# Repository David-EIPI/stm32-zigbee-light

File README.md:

# stm32-zigbee-light
Remotely controlled deck light using a STM32WB55 and Homeassistant integration.

## Overview
This project is yet another automatic outdoor light. Some time back I have purchased a porch light with motion sensor, model 4190 by HeathZenith. My unit apparently was faulty, at least I could not make it to turn on and off at the right time. Instead of returning I have decided to turn it into a practice project to play with Zigbee and Homeassistant.

## Firmware
The firmware is written in C using STM32CubeIDE. I have preserved the link to the IOC file adding a few CPP macro hacks in the source.

The firmware implements 6 endpoints and 12 clusters:
- 6 Analog Output clusters
- 3 Binary Input clusters
- 1 Multistate Value cluster
- 1 Illuminance Measurement cluster
- 1 Temperature Measurement cluster

Zero crossing detection using STM32 timers is described in a [separate file](zerocrossing.md).

## Hardware
The replacement PCB board copies the shape of the original control board and fits in the same enclosure without modifications.

Also the switches, the pot, and the sensors are positioned to fit the holes in the enclosure and the outer case. The firmware reads the switches when not connected to the Zigbee network, otherwise remote settings take precedence.

My setup uses STM32WB55 based board from WeAct, but any other 3.3V controller can be used.

The light is controlled with the triac dimmer triggered by the optocoupler. This configuration is only capable of leading-edge dimming, so a compatible bulb should be used. Phase adjustment (in ms) is needed to compensate for the zero-crossing detection circuit latency (mainly due to the optocoupler).

## ZHA quirck
Homeassistant's Zigbee integration recognizes most clusters from the firmware except the Multistate Value. The quirk file should be copied to the Homeassistant zha_quirk directory for proper work.

(I have edited the auto-generated entity labels visible in the screenshot.)

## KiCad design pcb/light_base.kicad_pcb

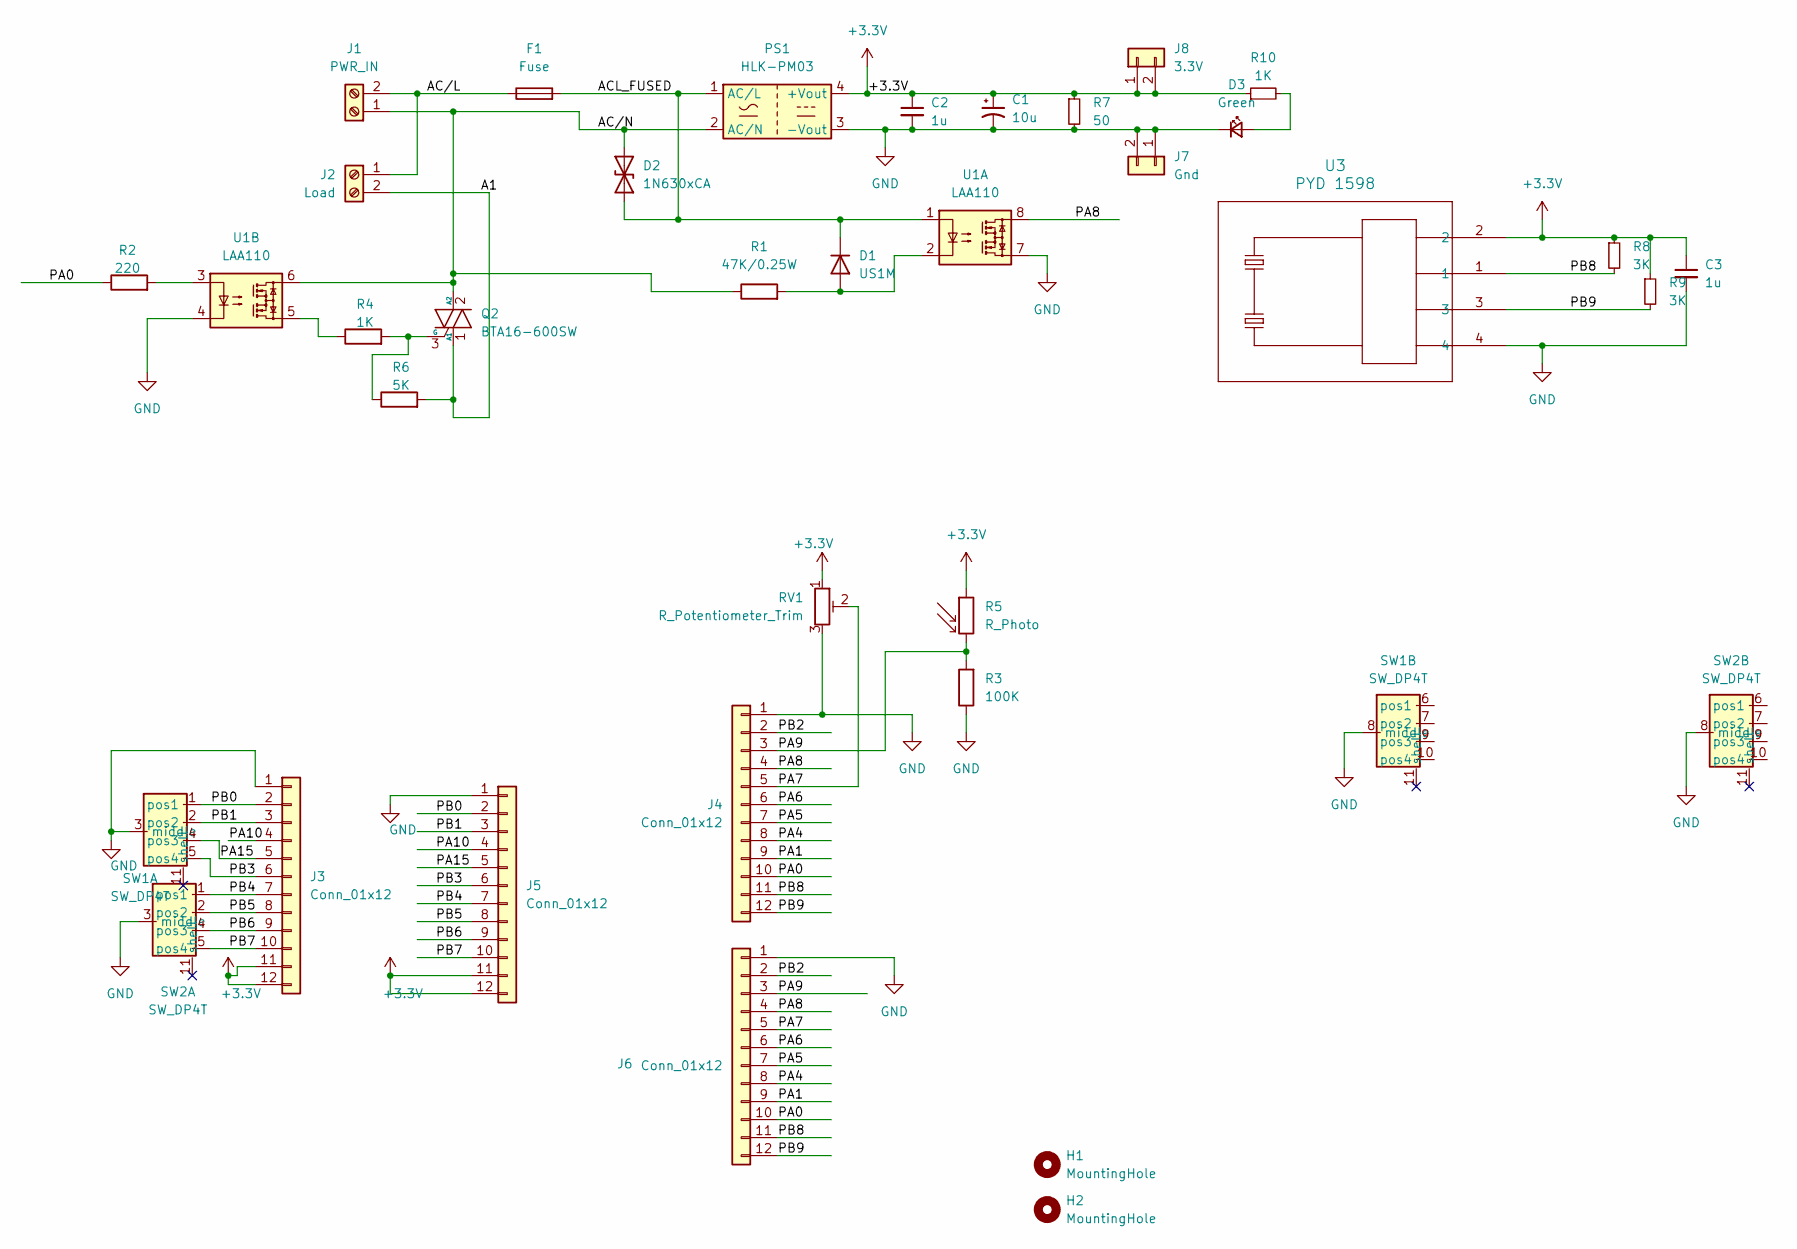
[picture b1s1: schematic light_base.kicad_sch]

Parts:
C1: 10u; CP_Radial_D5.0mm_P2.50mm
C2, C3: 1u; C_0805_2012Metric_Pad1.18x1.45mm_HandSolder
D1: US1M; D_SMA
D2: 1N630xCA; RV_Disc_D9mm_W6.1mm_P5mm
D3: Green; LED_0603_1608Metric_Pad1.05x0.95mm_HandSolder
F1: Fuse; R_Axial_DIN0614_L14.3mm_D5.7mm_P15.24mm_Horizontal
H1, H2: MountingHole; MountingHole_6.4mm_M6
J1: PWR_IN; JST_NV_B02P-NV_1x02_P5.00mm_Vertical
J2: Load; JST_NV_B02P-NV_1x02_P5.00mm_Vertical
J3, J4, J5, J6: Conn_01x12; JST_EH_B12B-EH-A_1x12_P2.50mm_Vertical
J7: Gnd; Molex_KK-254_AE-6410-02A_1x02_P2.54mm_Vertical
J8: 3.3V; Molex_KK-254_AE-6410-02A_1x02_P2.54mm_Vertical
PS1: HLK-PM03; Converter_ACDC_Hi-Link_HLK-PMxx
Q2: BTA16-600SW; TO-220-3_Vertical
R1: 47K/0.25W; R_1206_3216Metric_Pad1.30x1.75mm_HandSolder
R2: 220; R_0603_1608Metric_Pad0.98x0.95mm_HandSolder
R3: 100K; R_0603_1608Metric_Pad0.98x0.95mm_HandSolder
R4: 1K; R_1206_3216Metric_Pad1.30x1.75mm_HandSolder
R5: R_Photo; R_LDR_7x6mm_P5.1mm_Vertical
R6: 5K; R_1206_3216Metric_Pad1.30x1.75mm_HandSolder
R7: 50; R_0805_2012Metric_Pad1.20x1.40mm_HandSolder
R8, R9: 3K; R_0603_1608Metric_Pad0.98x0.95mm_HandSolder
R10: 1K; R_0603_1608Metric_Pad0.98x0.95mm_HandSolder
RV1: R_Potentiometer_Trim; Potentiometer_Piher_PT-10-V10_Vertical_Hole
SW1, SW2: SW_DP4T
U1: LAA110; DIP-8_W7.62mm
U3: PYD 1598; SENSE4_PYD 1598_EXT

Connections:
+3.3V: C1.1, C2.1, C3.1, J3.11, J3.12, J5.11, J5.12, J8.1, J8.2, PS1.4 (+Vout), R5.1, R7.1, R8.1, R9.1, R10.1, RV1.1, U3.2
/A1: J2.2, Q2.1 (A1), R6.2
/ACL_FUSED: D1.1 (K), D2.1 (A1), F1.2, PS1.1 (AC/L), U1.1
/AC/L: F1.1, J1.2, J2.1
/AC/N: D2.2 (A2), J1.1, PS1.2 (AC/N), Q2.2 (A2), R1.1, U1.6
/PA0: J4.10, J6.10, R2.1
/PA1: J4.9, J6.9
/PA4: J4.8, J6.8
/PA5: J4.7, J6.7
/PA6: J4.6, J6.6
/PA7: J4.5, J6.5, RV1.2
/PA8: J4.4, J6.4, U1.8
/PA9: J4.3, J6.3, R3.2, R5.2
/PA10: J3.4, J5.4
/PA15: J3.5, J5.5, SW1.4 (pos3)
/PB0: J3.2, J5.2, SW1.1 (pos1)
/PB1: J3.3, J5.3, SW1.2 (pos2)
/PB2: J4.2, J6.2
/PB3: J3.6, J5.6, SW1.5 (pos4)
/PB4: J3.7, J5.7, SW2.1 (pos1)
/PB5: J3.8, J5.8, SW2.2 (pos2)
/PB6: J3.9, J5.9, SW2.4 (pos3)
/PB7: J3.10, J5.10, SW2.5 (pos4)
/PB8: J4.11, J6.11, R8.2, U3.1
/PB9: J4.12, J6.12, R9.2, U3.3
GND: C1.2, C2.2, C3.2, D3.1 (K), J3.1, J4.1, J5.1, J6.1, J7.1, J7.2, PS1.3 (-Vout), R3.1, R7.2, RV1.3, SW1.3 (middle), SW1.8 (middle), SW2.3 (middle), SW2.8 (middle), U1.4, U1.7, U3.4
unnamed: D1.2 (A), R1.2, U1.2
unnamed: D3.2 (A), R10.2
unnamed: Q2.3 (G), R4.2, R6.1
unnamed: R2.2, U1.3
unnamed: R4.1, U1.5

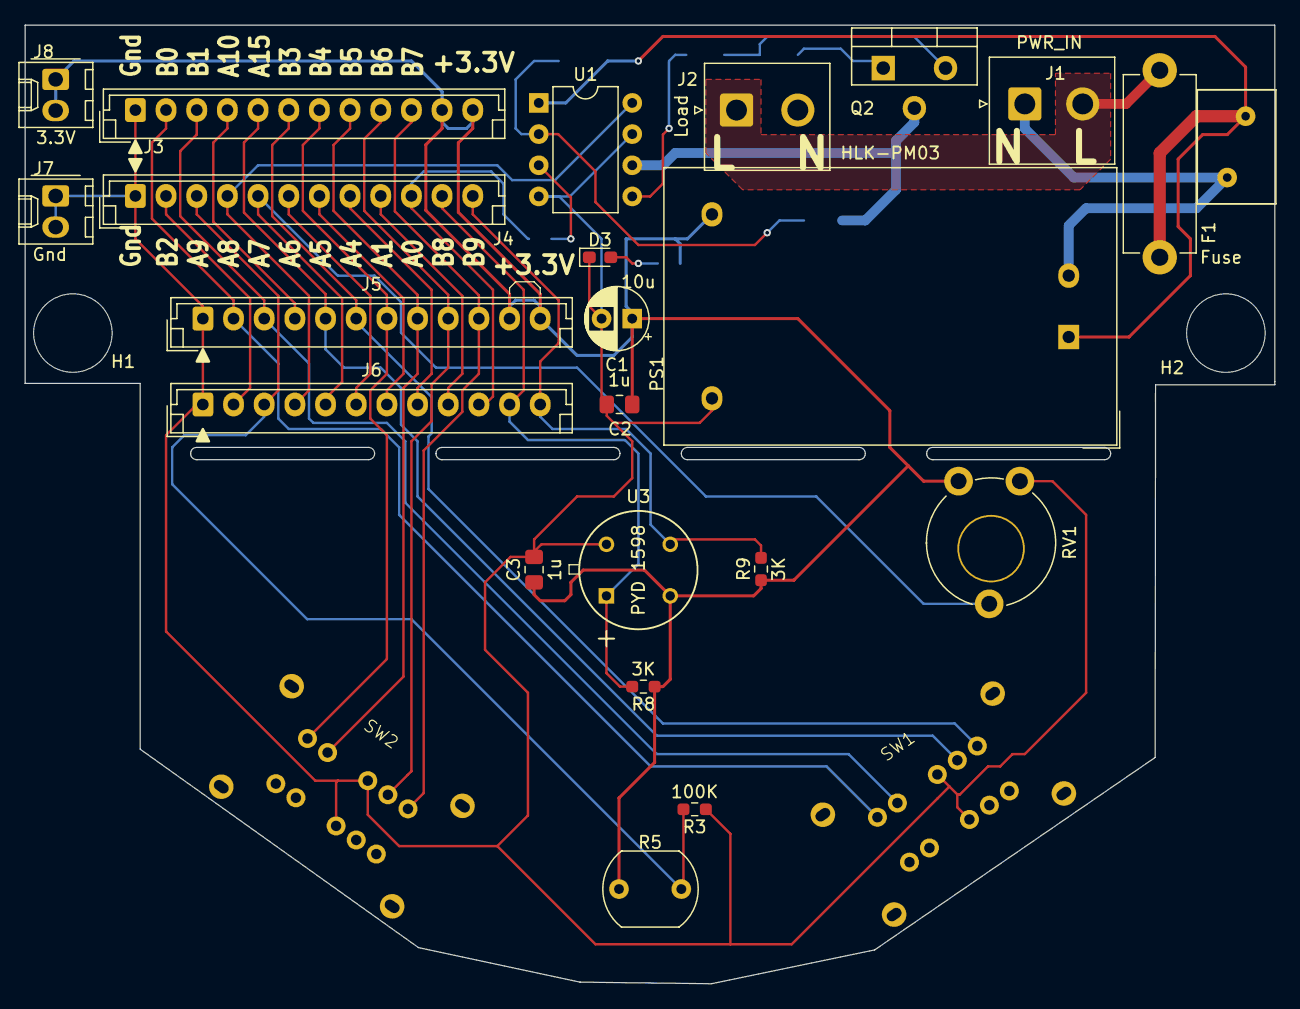
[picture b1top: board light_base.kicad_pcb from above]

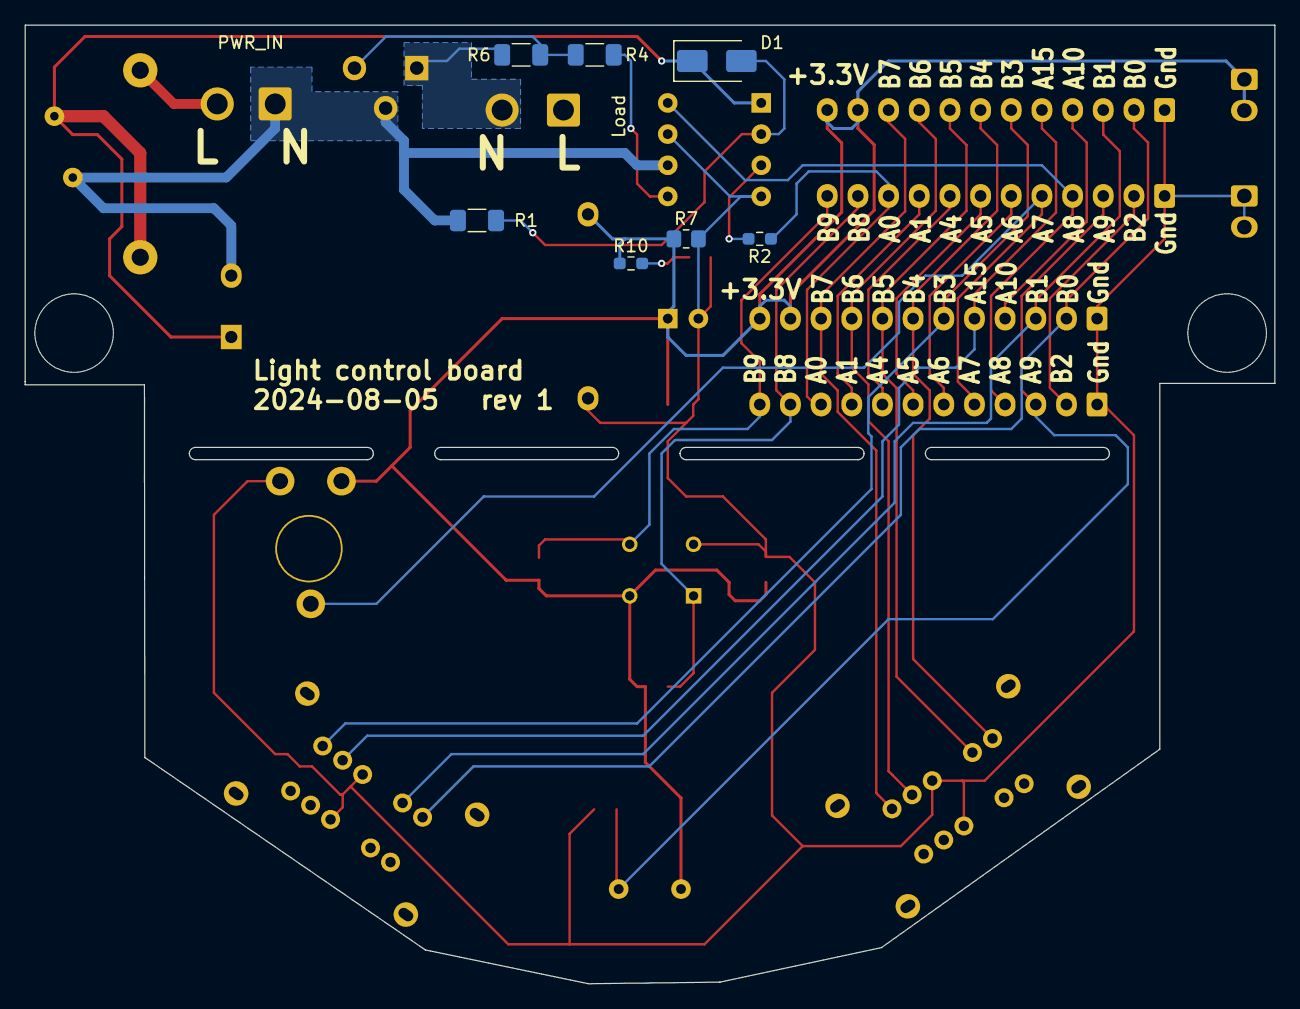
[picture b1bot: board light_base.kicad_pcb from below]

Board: 2 copper layers, 101.9 x 78.1 mm, 34 parts (7 on the bottom side), 31 nets.

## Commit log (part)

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2024-10-25 Initial upload.
2024-10-26 Update copyright headers in some files.
2024-10-26 Add PCB design files
2024-10-26 Add ZHA quirk file
2024-10-27 Add the detailed project description.
2025-02-15 Support join and rejoin without restart.
    Search and join a network immediately after leave requested, no restart
    needed.
    Initiate re-join if link to the parent node is lost.
    Remove unused code, add more annotations.
2025-02-15 Add detailed description of the zero crossing detector.
2025-03-14 Changes related to Zigbee connectivity.
    Remove NwkRejoin code - M0 FW seems to handle leave-rejoin well.
    Increase TX Power.
    Remove cost threshold for parent connection.
    Reduce persistense frequency.
2025-03-16 Switch Zigbee device type to router. This seems to result in a more stable connection.
    Change Phase Correction units to microseconds. Add support for
    microseconds to ZHA using quirk file.
    Remove some unused code.
2025-06-21 Remove reference to const.UNITS since zigpy now implements BACNet units.
2025-06-30 Improve ambient brightness response. Add daily auto-restart.
